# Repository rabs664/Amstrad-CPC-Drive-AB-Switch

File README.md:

# Amstrad-CPC-Drive-AB-Switch
 
Some Amstrad CPC software will not run on an external drive, Drive B, as it expects to run on the internal drive, Drive A.

This can be rectified by adding a header to the floppy ribbon cable and inserting a small switch to pull Drive Select 1 low.

Information regarding this can be found in the [CPCWiki Guide on how to connect a 3.5" drive to a CPC 6128](https://www.cpcwiki.eu/index.php?title=Guide_on_how_to_connect_a_3.5%22_drive_to_a_CPC6128/664)

This CPCWiki guide discusses an option to make the external drive the Primary Drive by connecting pin 11 to 12 on the cable where pin 12 is the Shugart standard numbering system for Drive Select 1, see [CPCWkiki Guide for the 2nd disc drive connector](https://www.cpcwiki.eu/index.php/Connector:2nd_disc_drive_(CPC664,_CPC6128,_CPC6128%2B)). Pin 11 is GND.

However, adding a header and switch is not always an option for a user.

This small PCB effectively acts as the switch in the ribbon cable, pulling Drive Select 1 low and allowing software which expects to run on Drive A, to run on Drive B.

The PCB then sits between the second floppy drive edge connector and the floppy drive ribbon cable.

>[!IMPORTANT]
>However, there are some restrictions on its use.
>Primairly you cannot have anything inserted into Drive A when the switch is in the ON position but also the switch should only be moved when the CPC is OFF.

>[!CAUTION]
>USE AT YOUR OWN RISK.
>There is always the risk that the switch can cause harm to your CPC. Although I have tested the switch, there is no guarantee that it will work properly under all circumstances.

>[!NOTE]
>This repository contains the associated Kicad project and Gerber files should you want to create the switch. A DigiKey list for the switch and edge connector can be found [here](https://www.digikey.co.uk/en/mylists/list/OB2QHATDFZ). Although the switch is not an ideal fit.

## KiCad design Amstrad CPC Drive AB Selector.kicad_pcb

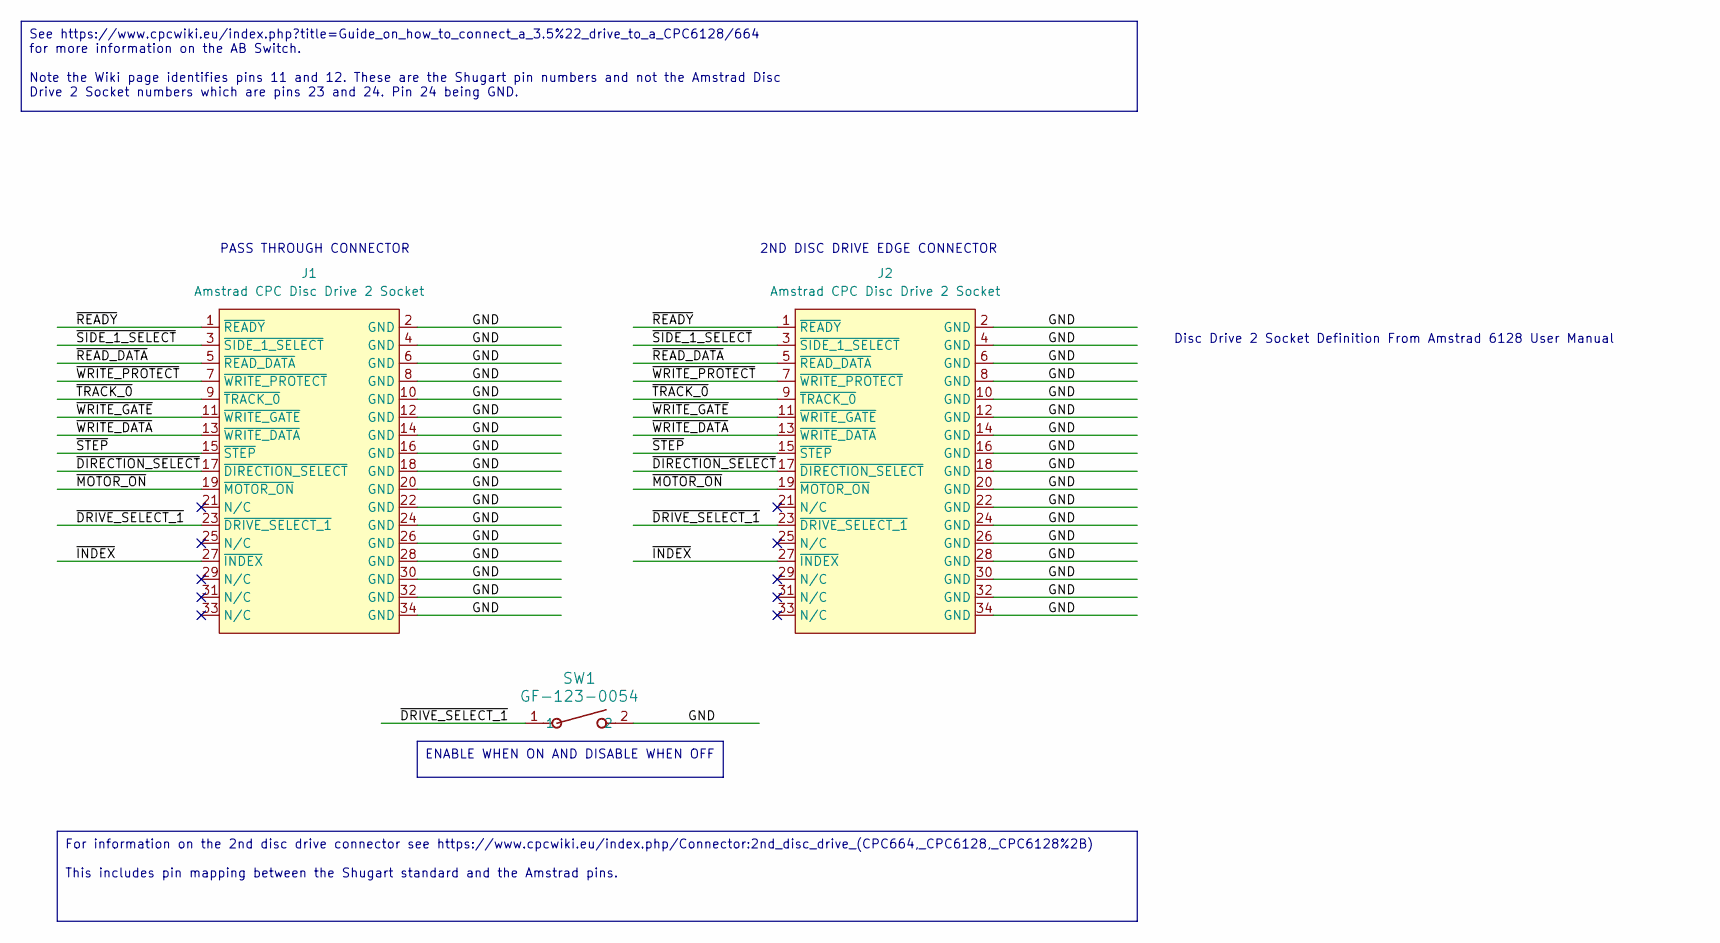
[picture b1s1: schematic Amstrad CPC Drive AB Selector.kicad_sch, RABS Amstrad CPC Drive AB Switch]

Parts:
J1, J2: Amstrad CPC Disc Drive 2 Socket; Amstrad_CPC_Disc_Drive_2_socket
SW1: GF-123-0054; SW2_GF-123-0054_CWI

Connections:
/GND: J1.2 (GND), J1.4 (GND), J1.6 (GND), J1.8 (GND), J1.10 (GND), J1.12 (GND), J1.14 (GND), J1.16 (GND), J1.18 (GND), J1.20 (GND), J1.22 (GND), J1.24 (GND), J1.26 (GND), J1.28 (GND), J1.30 (GND), J1.32 (GND), J1.34 (GND), J2.2 (GND), J2.4 (GND), J2.6 (GND), J2.8 (GND), J2.10 (GND), J2.12 (GND), J2.14 (GND), J2.16 (GND), J2.18 (GND), J2.20 (GND), J2.22 (GND), J2.24 (GND), J2.26 (GND), J2.28 (GND), J2.30 (GND), J2.32 (GND), J2.34 (GND), SW1.2
/~DIRECTION_SELECT: J1.17 (~DIRECTION_SELECT), J2.17 (~DIRECTION_SELECT)
/~DRIVE_SELECT_1: J1.23 (~DRIVE_SELECT_1), J2.23 (~DRIVE_SELECT_1), SW1.1
/~INDEX: J1.27 (~INDEX), J2.27 (~INDEX)
/~MOTOR_ON: J1.19 (~MOTOR_ON), J2.19 (~MOTOR_ON)
/~READY: J1.1 (~READY), J2.1 (~READY)
/~READ_DATA: J1.5 (~READ_DATA), J2.5 (~READ_DATA)
/~SIDE_1_SELECT: J1.3 (~SIDE_1_SELECT), J2.3 (~SIDE_1_SELECT)
/~STEP: J1.15 (~STEP), J2.15 (~STEP)
/~TRACK_0: J1.9 (~TRACK_0), J2.9 (~TRACK_0)
/~WRITE_DATA: J1.13 (~WRITE_DATA), J2.13 (~WRITE_DATA)
/~WRITE_GATE: J1.11 (~WRITE_GATE), J2.11 (~WRITE_GATE)
/~WRITE_PROTECT: J1.7 (~WRITE_PROTECT), J2.7 (~WRITE_PROTECT)

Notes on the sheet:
See https://www.cpcwiki.eu/index.php?title=Guide_on_how_to_connect_a_3.5%22_drive_to_a_CPC6128/664 for more information on the AB Switch. Note the Wiki page identifies pins 11 and 12. These are the Shugart pin numbers and not the Amstrad Disc Drive 2 Socket numbers which are pins 23 and 24. Pin 24 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
For information on the 2nd disc drive connector see https://www.cpcwiki.eu/index.php/Connector:2nd_disc_drive_(CPC664,_CPC6128,_CPC6128%2B) This includes pin mapping between the Shugart standard and the Amstrad pins.
ENABLE WHEN ON AND DISABLE WHEN OFF
PASS THROUGH CONNECTOR
2ND DISC DRIVE EDGE CONNECTOR
Disc Drive 2 Socket Definition From Amstrad 6128 User Manual

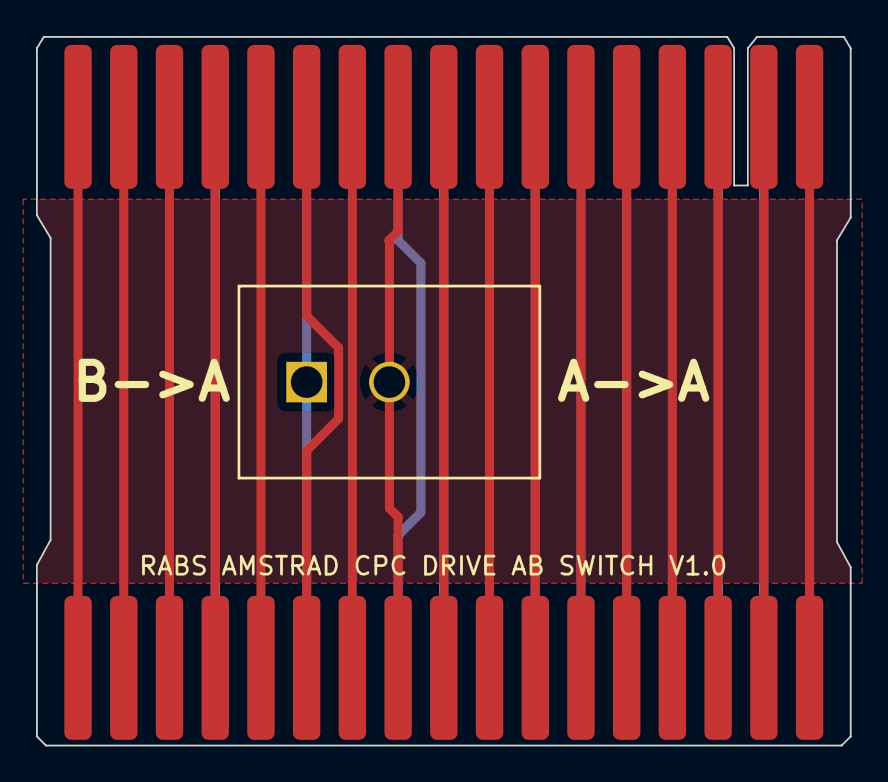
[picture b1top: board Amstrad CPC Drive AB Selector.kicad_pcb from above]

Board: 2 copper layers, 45.2 x 39.4 mm, 3 parts (0 on the bottom side), 13 nets.

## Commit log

2025-06-23 Added footprint for Disc Drive 2 socket
2025-06-23 Added Disc Drive 2 Symbol library
2025-11-03 Update usage instructions for drive switch
    Clarified usage restrictions for the drive switch in the README.
2025-11-03 Update restrictions note in README.md
    Removed specific link to CPCWiki Guide from restrictions section.
